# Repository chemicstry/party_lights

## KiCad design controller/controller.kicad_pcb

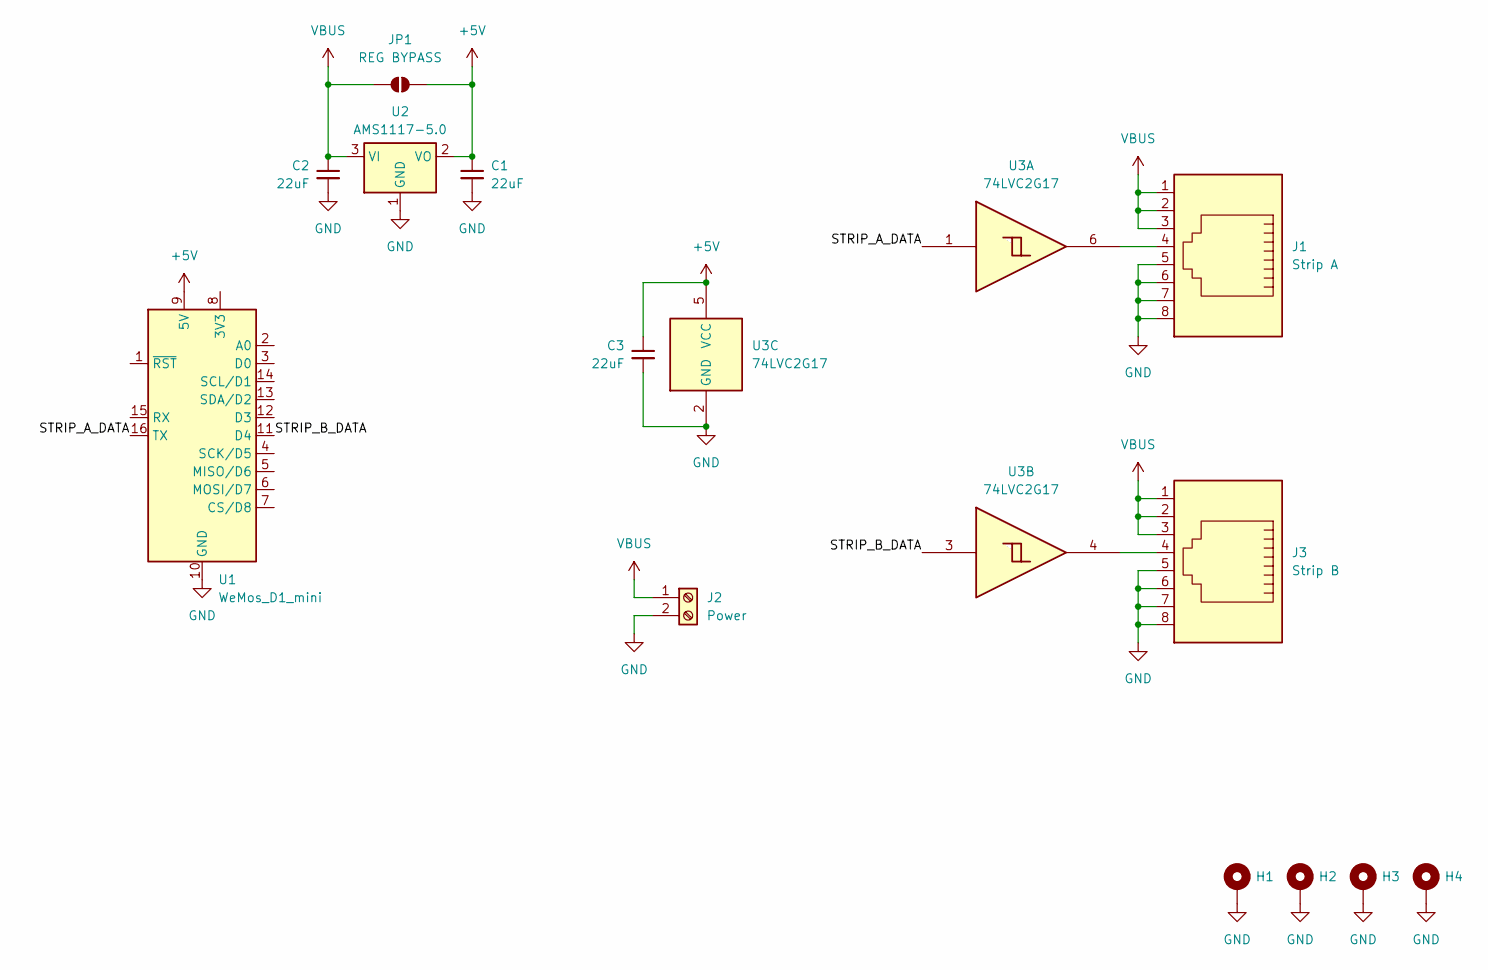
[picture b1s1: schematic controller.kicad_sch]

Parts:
C1, C2, C3: 22uF; C_0805_2012Metric
H1, H2, H3, H4: MountingHole_Pad; MountingHole_3.2mm_M3_Pad
J1: Strip A; RJ45_Amphenol_54602-x08_Horizontal; MPN MTJ-885X1
J2: Power; TerminalBlock_bornier-2_P5.08mm
J3: Strip B; RJ45_Amphenol_54602-x08_Horizontal; MPN MTJ-885X1
JP1: REG BYPASS; SolderJumper-2_P1.3mm_Open_RoundedPad1.0x1.5mm
U1: WeMos_D1_mini; WEMOS_D1_mini_light
U2: AMS1117-5.0; SOT-223-3_TabPin2
U3: 74LVC2G17; SOT-23-6

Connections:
+5V: C1.1, C3.1, JP1.2 (B), U1.9 (5V), U2.2 (VO), U3.5 (VCC)
/STRIP_A_DATA: U1.16 (TX), U3.1
/STRIP_B_DATA: U1.11 (D4), U3.3
GND: C1.2, C2.2, C3.2, H1.1, H2.1, H3.1, H4.1, J1.5, J1.6, J1.7, J1.8, J2.2, J3.5, J3.6, J3.7, J3.8, U1.10 (GND), U2.1 (GND), U3.2 (GND)
unnamed: J1.4, U3.6
unnamed: J3.4, U3.4
VBUS: C2.1, J1.1, J1.2, J1.3, J2.1, J3.1, J3.2, J3.3, JP1.1 (A), U2.3 (VI)

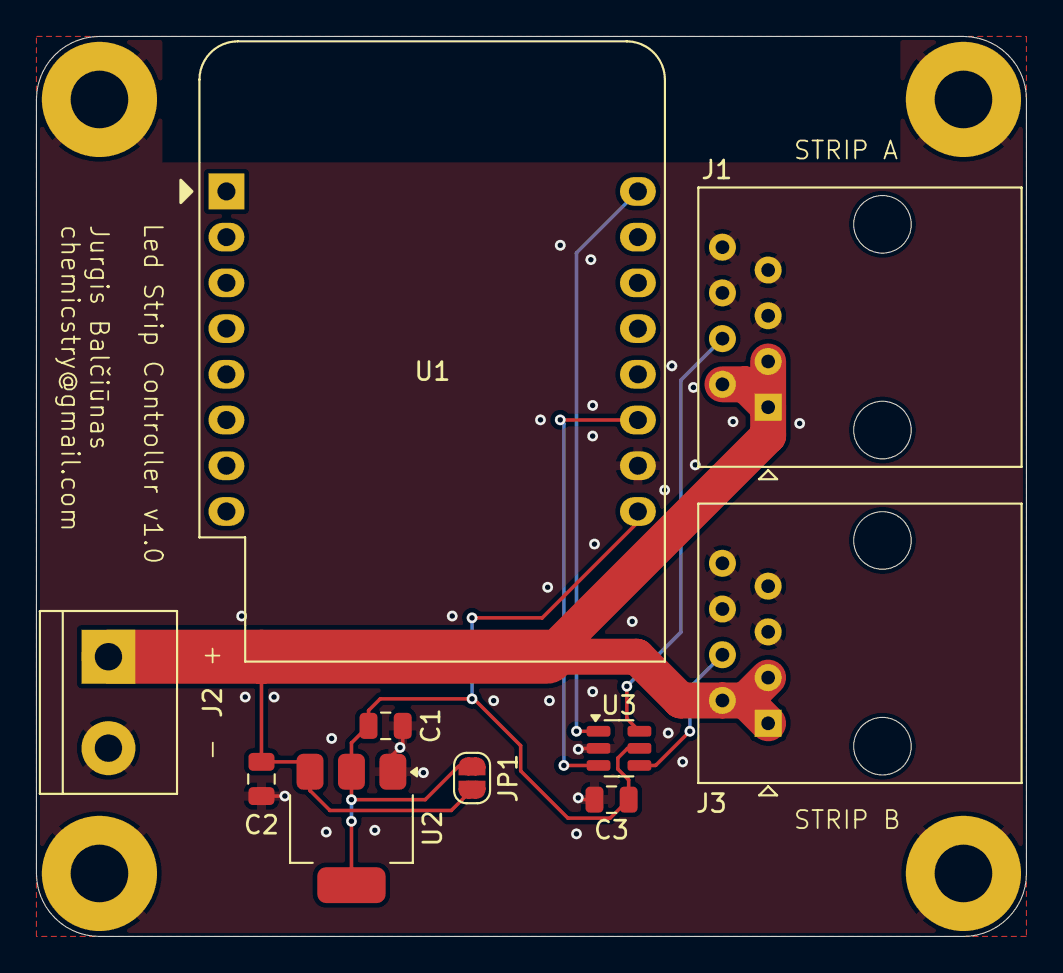
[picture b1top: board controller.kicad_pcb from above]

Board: 2 copper layers, 55.0 x 50.0 mm, 14 parts (0 on the bottom side), 7 nets.

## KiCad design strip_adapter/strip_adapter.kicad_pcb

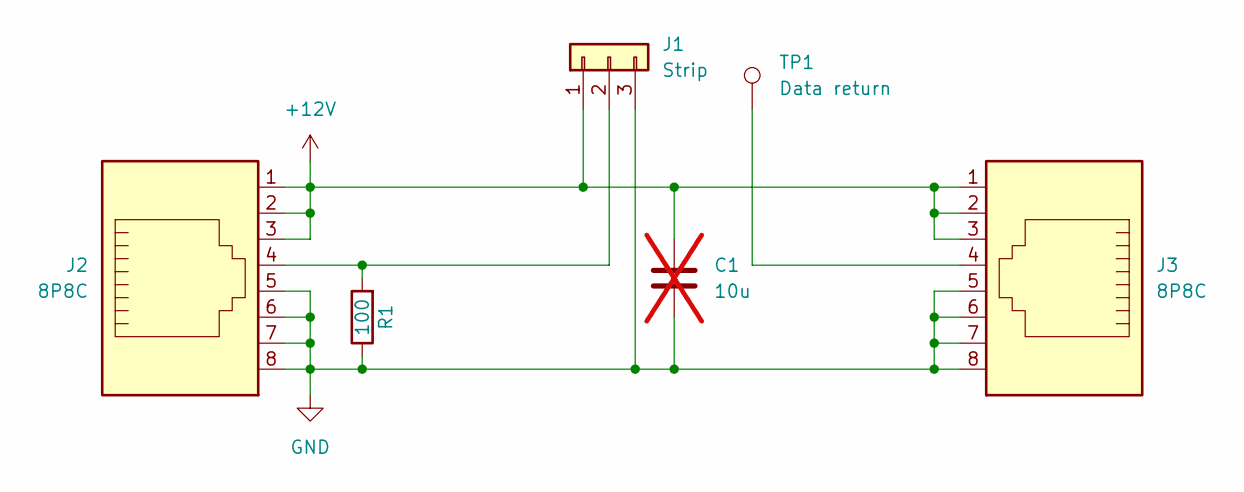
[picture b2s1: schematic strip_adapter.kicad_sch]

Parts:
C1: 10u; C_0603_1608Metric; not fitted
J1: Strip; led_strip_3pin
J2, J3: 8P8C; RJ45_Amphenol_54602-x08_Horizontal; MPN MTJ-885X1
R1: 100; R_0603_1608Metric
TP1: Data return; TestPoint_Pad_1.5x1.5mm

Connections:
+12V: C1.1, J1.1, J2.1, J2.2, J2.3, J3.1, J3.2, J3.3
GND: C1.2, J1.3, J2.5, J2.6, J2.7, J2.8, J3.5, J3.6, J3.7, J3.8, R1.1
unnamed: J1.2, J2.4, R1.2
unnamed: J3.4, TP1.1

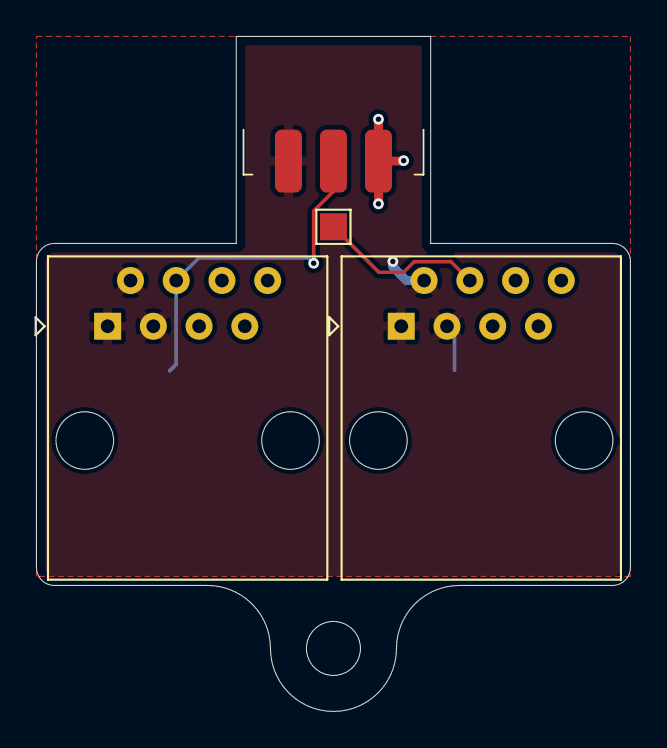
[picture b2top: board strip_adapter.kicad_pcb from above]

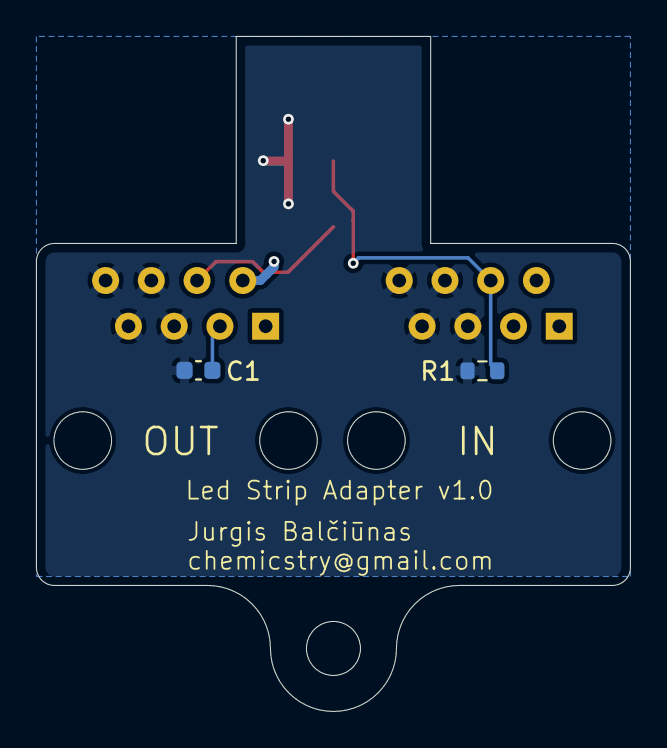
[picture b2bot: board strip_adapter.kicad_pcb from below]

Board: 2 copper layers, 33.0 x 37.5 mm, 6 parts (2 on the bottom side), 4 nets.
